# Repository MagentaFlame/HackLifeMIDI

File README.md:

Hey guys!
For 3rd week of Hack Life, I decided to go with the starter project, a MIDI keyboard, because I'm not very experienced in PCBs and fear for my safety lolll

Okay, so here goes...

The schematic:

I play piano, so not having the full range really does make me sad... But I did want to add more features so I sacrificed the whole octave for volume lol. 12 keys, 1 toggle switch (volume/octave changes) and 1 button switch (change between volume or octave change)

The PCB:
front:

back:

together:

Okay... so was it so surprising that this is League of Legends themed? So far every week of Hack Life I've made it LOL themed...
I have K/DA symbols on the front (fox Ahri, the Kaisa back thingy, Evelynn's K/DA skin ribbon end, Akali kama) and their newest title song "Firestarter" on the back + fire.

The code:
no screenshot, but explanation - initial state is volume medium (velocity 64), octaves regular range, the toggle will change the octaves. After press button once, toggle will become a volume up/down switch.
dang it was hard to code... I had to pull up the python knowledge from the depths of my brain (middle school). I guess refreshing it was easier than actually learning it.

Here's a screenshot of the BOM:

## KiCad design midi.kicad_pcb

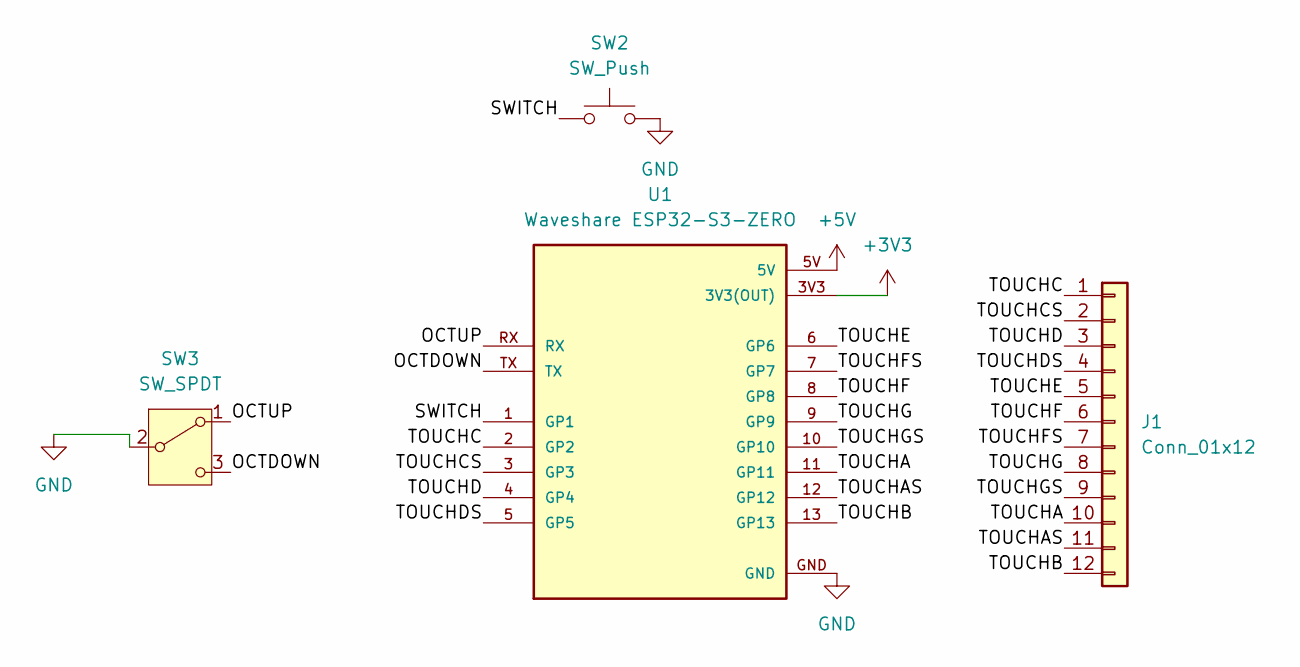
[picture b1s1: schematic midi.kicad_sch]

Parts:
J1: Conn_01x12; capacitivekeys
SW2: SW_Push; SW_Cherry_MX_1.00u_PCB
SW3: SW_SPDT; SW_NKK_G1xJP
U1: Waveshare ESP32-S3-ZERO; Waveshare ESP32-S3-Zero; PARTREV NA

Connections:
+3V3: U1.3V3 (3V3(OUT))
+5V: U1.5V
/OCTDOWN: SW3.3 (C), U1.TX
/OCTUP: SW3.1 (A), U1.RX
/SWITCH: SW2.1, U1.1 (GP1)
/TOUCHA: J1.10, U1.11 (GP11)
/TOUCHAS: J1.11, U1.12 (GP12)
/TOUCHB: J1.12, U1.13 (GP13)
/TOUCHC: J1.1, U1.2 (GP2)
/TOUCHCS: J1.2, U1.3 (GP3)
/TOUCHD: J1.3, U1.4 (GP4)
/TOUCHDS: J1.4, U1.5 (GP5)
/TOUCHE: J1.5, U1.6 (GP6)
/TOUCHF: J1.6, U1.8 (GP8)
/TOUCHFS: J1.7, U1.7 (GP7)
/TOUCHG: J1.8, U1.9 (GP9)
/TOUCHGS: J1.9, U1.10 (GP10)
GND: SW2.2, SW3.2 (B), U1.GND

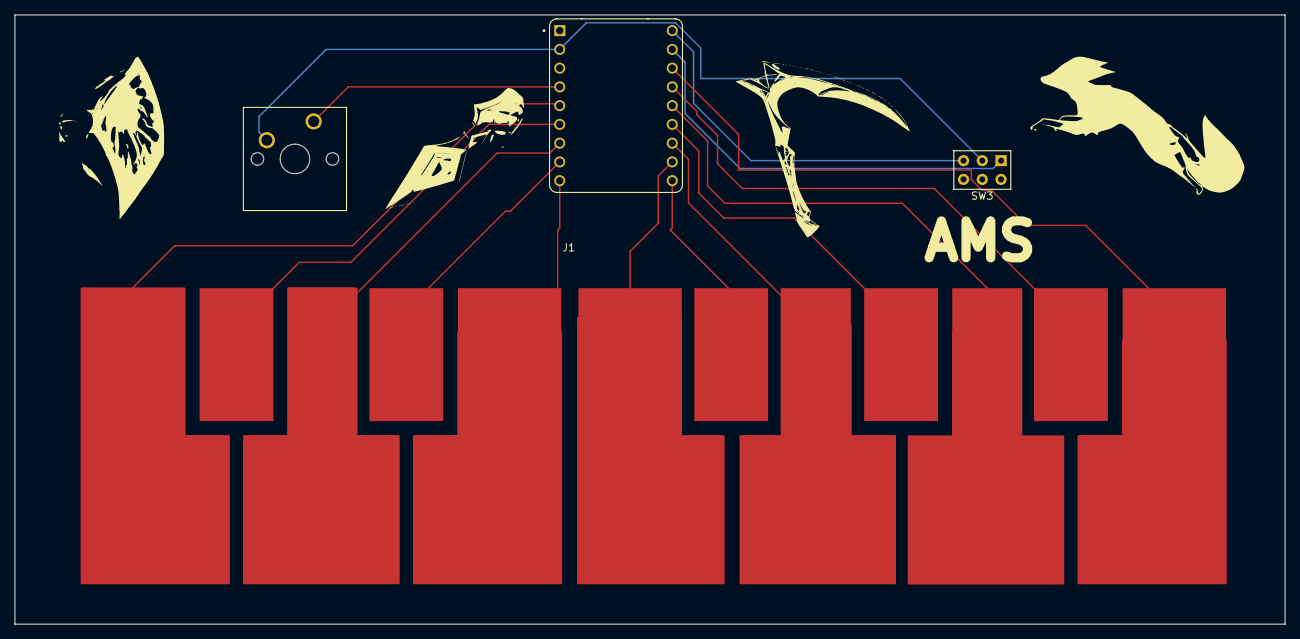
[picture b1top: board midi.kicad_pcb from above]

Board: 2 copper layers, 172.0 x 82.5 mm, 4 parts (0 on the bottom side), 16 nets.
